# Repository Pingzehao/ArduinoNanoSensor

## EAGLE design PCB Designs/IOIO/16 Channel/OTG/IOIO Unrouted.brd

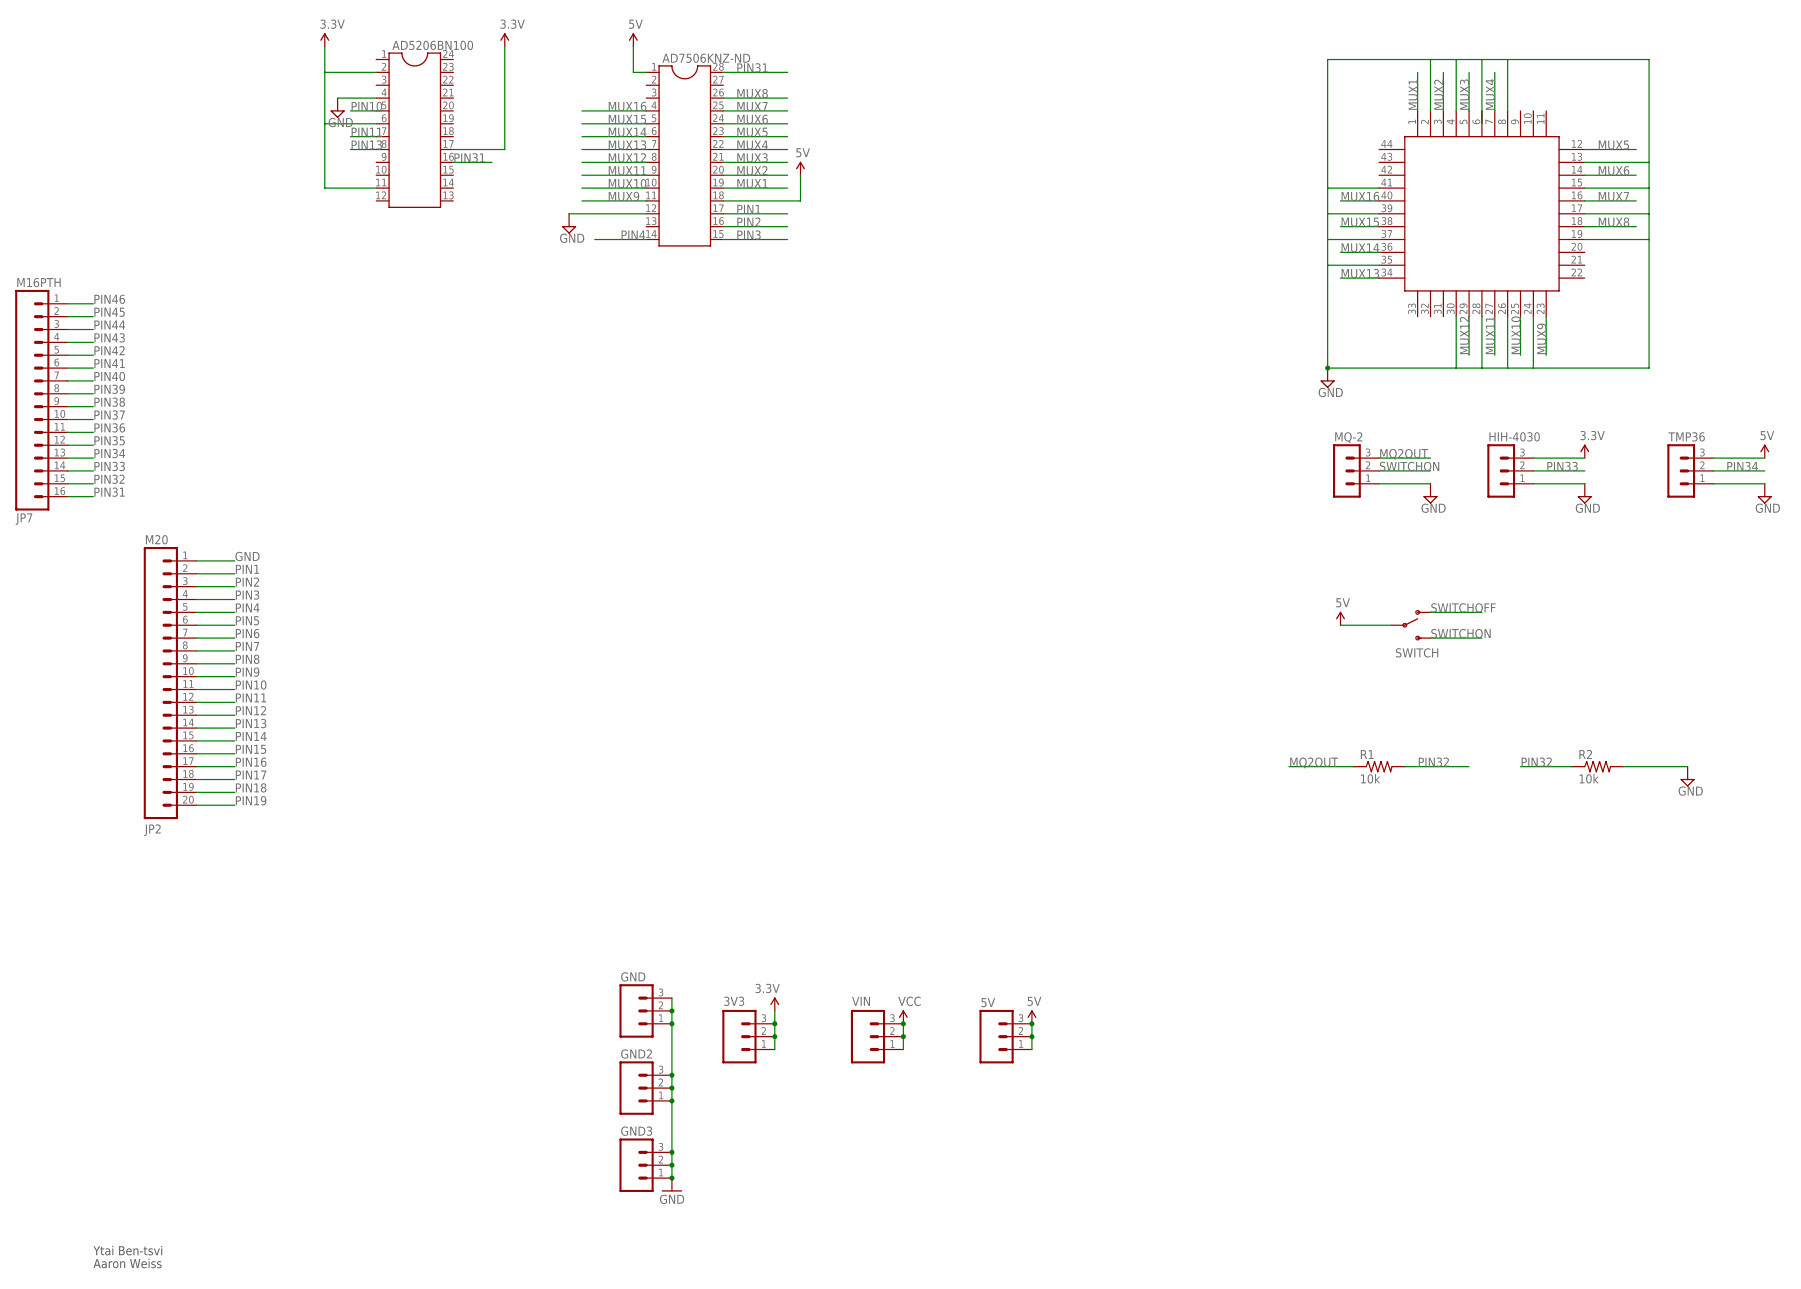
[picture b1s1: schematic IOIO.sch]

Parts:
3V3, 5V: M03PTH; 1X03
AD5206BN100: DIL24-3
AD7506KNZ-ND: DIL28; DIL28-6
GND, GND2, GND3: M03PTH; 1X03
HIH-4030: MA03-1
JP2: M20; 1X20
JP7: M16PTH; 1X16
MQ-2: MA03-1
R1, R2: 10k; 0207/7
SWITCH: SWITCH-SPSTPTH; SWITCH-SPDT
TMP36: MA03-1
U$1: S44
VIN: M03PTH; 1X03

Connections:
3.3V: 3V3.1, 3V3.2, 3V3.3, AD5206BN100.2, AD5206BN100.6, AD5206BN100.11, AD5206BN100.17, HIH-4030.3
5V: 5V.1, 5V.2, 5V.3, AD7506KNZ-ND.1, AD7506KNZ-ND.18, SWITCH.2, TMP36.3
GND: AD5206BN100.4, AD7506KNZ-ND.12, GND.1, GND.2, GND.3, GND2.1, GND2.2, GND2.3, GND3.1, GND3.2, GND3.3, HIH-4030.1, JP2.1, MQ-2.1, R2.2, TMP36.1, U$1.2, U$1.4, U$1.8, U$1.13, U$1.15, U$1.17, U$1.19, U$1.24, U$1.26, U$1.28, U$1.30, U$1.35, U$1.37, U$1.39, U$1.41
MQ2OUT: MQ-2.3, R1.1
MUX1: AD7506KNZ-ND.19, U$1.1
MUX2: AD7506KNZ-ND.20, U$1.3
MUX3: AD7506KNZ-ND.21, U$1.5
MUX4: AD7506KNZ-ND.22, U$1.7
MUX5: AD7506KNZ-ND.23, U$1.12
MUX6: AD7506KNZ-ND.24, U$1.14
MUX7: AD7506KNZ-ND.25, U$1.16
MUX8: AD7506KNZ-ND.26, U$1.18
MUX9: AD7506KNZ-ND.11, U$1.23
MUX10: AD7506KNZ-ND.10, U$1.25
MUX11: AD7506KNZ-ND.9, U$1.27
MUX12: AD7506KNZ-ND.8, U$1.29
MUX13: AD7506KNZ-ND.7, U$1.34
MUX14: AD7506KNZ-ND.6, U$1.36
MUX15: AD7506KNZ-ND.5, U$1.38
MUX16: AD7506KNZ-ND.4, U$1.40
PIN1: AD7506KNZ-ND.17, JP2.2
PIN2: AD7506KNZ-ND.16, JP2.3
PIN3: AD7506KNZ-ND.15, JP2.4
PIN4: AD7506KNZ-ND.14, JP2.5
PIN5: JP2.6
PIN6: JP2.7
PIN7: JP2.8
PIN8: JP2.9
PIN9: JP2.10
PIN10: AD5206BN100.5, JP2.11
PIN11: AD5206BN100.7, JP2.12
PIN12: JP2.13
PIN13: AD5206BN100.8, JP2.14
PIN14: JP2.15
PIN15: JP2.16
PIN16: JP2.17
PIN17: JP2.18
PIN18: JP2.19
PIN19: JP2.20
PIN31: AD5206BN100.16, AD7506KNZ-ND.28, JP7.16
PIN32: JP7.15, R1.2, R2.1
PIN33: HIH-4030.2, JP7.14
PIN34: JP7.13, TMP36.2
PIN35: JP7.12
PIN36: JP7.11
PIN37: JP7.10
PIN38: JP7.9
PIN39: JP7.8
PIN40: JP7.7
PIN41: JP7.6
PIN42: JP7.5
PIN43: JP7.4
PIN44: JP7.3
PIN45: JP7.2
PIN46: JP7.1
SWITCHOFF: SWITCH.1 (O)
SWITCHON: MQ-2.2, SWITCH.3 (S)
VCC: VIN.1, VIN.2, VIN.3

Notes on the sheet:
Ytai Ben-tsvi
Aaron Weiss

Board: 2 copper layers, 17 parts (0 on the bottom side), 33 nets, no tracks yet.

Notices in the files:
parts and their libraries:
SparkFun-Connectors: Licensing: CC v3.0 Share-Alike You are welcome to use this library for commercial purposes.
